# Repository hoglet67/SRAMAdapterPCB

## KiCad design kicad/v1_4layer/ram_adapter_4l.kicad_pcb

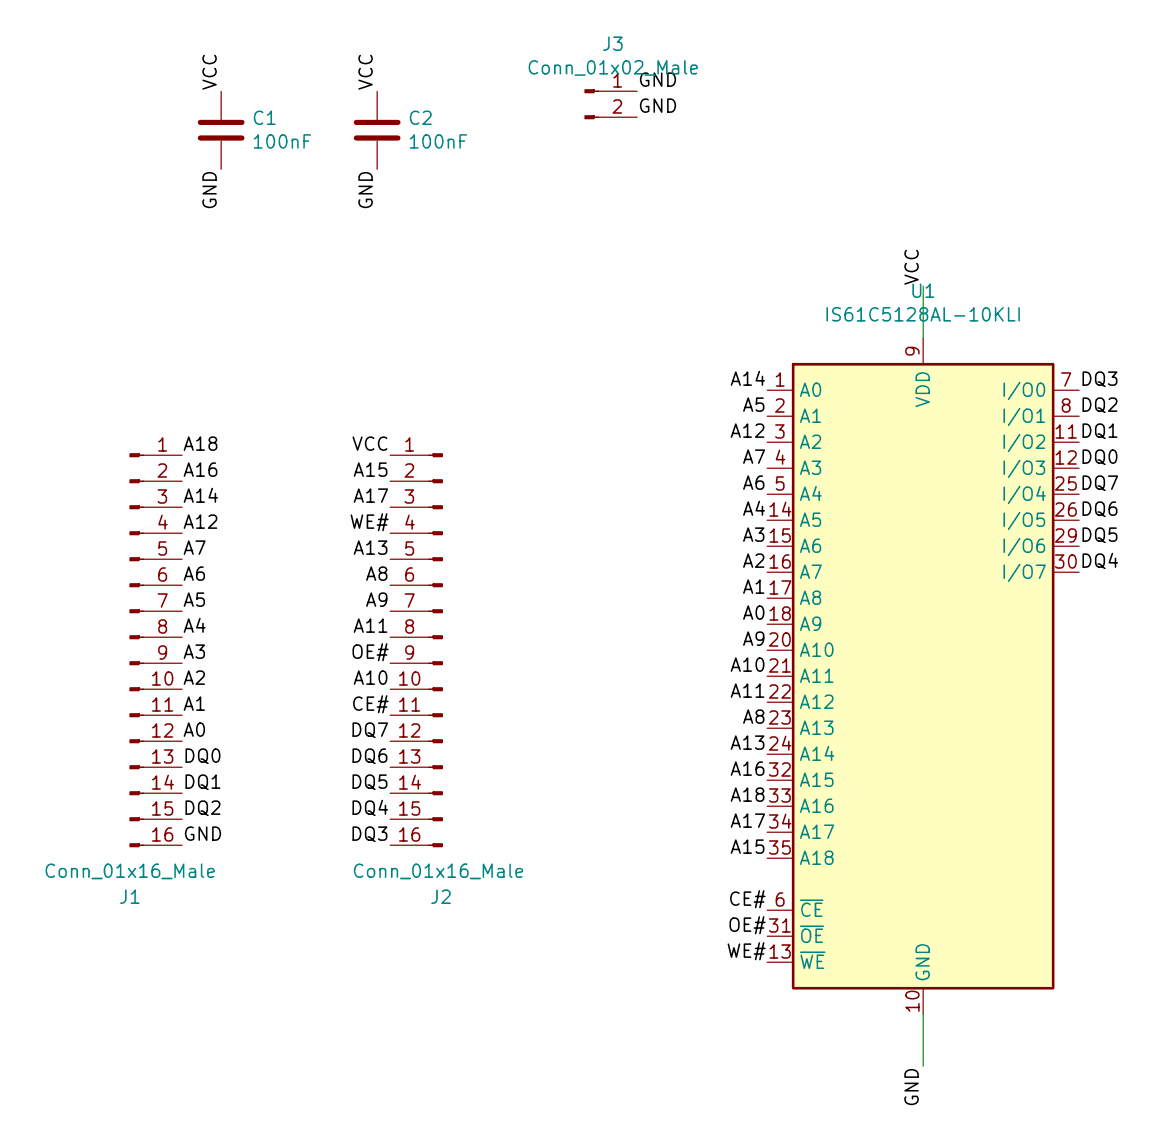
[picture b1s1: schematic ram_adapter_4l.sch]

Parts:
C1, C2: 100nF; C_0805_2012Metric
J1: Conn_01x16_Male; PinHeader_1x16_P2.54mm_Vertical
J2: Conn_01x16_Male; PinHeader_1x16_P2.54mm_VerticalAllRound
J3: Conn_01x02_Male; PinHeader_1x02_P2.54mm_Vertical
U1: IS61C5128AL-10KLI; SOJ-36_10.16x23.49mm_P1.27mm

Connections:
/A0: J1.12, U1.18 (A9)
/A1: J1.11, U1.17 (A8)
/A2: J1.10, U1.16 (A7)
/A3: J1.9, U1.15 (A6)
/A4: J1.8, U1.14 (A5)
/A5: J1.7, U1.2 (A1)
/A6: J1.6, U1.5 (A4)
/A7: J1.5, U1.4 (A3)
/A8: J2.6, U1.23 (A13)
/A9: J2.7, U1.20 (A10)
/A10: J2.10, U1.21 (A11)
/A11: J2.8, U1.22 (A12)
/A12: J1.4, U1.3 (A2)
/A13: J2.5, U1.24 (A14)
/A14: J1.3, U1.1 (A0)
/A15: J2.2, U1.35 (A18)
/A16: J1.2, U1.32 (A15)
/A17: J2.3, U1.34 (A17)
/A18: J1.1, U1.33 (A16)
/CE#: J2.11, U1.6 (~CE)
/DQ0: J1.13, U1.12 (I/O3)
/DQ1: J1.14, U1.11 (I/O2)
/DQ2: J1.15, U1.8 (I/O1)
/DQ3: J2.16, U1.7 (I/O0)
/DQ4: J2.15, U1.30 (I/O7)
/DQ5: J2.14, U1.29 (I/O6)
/DQ6: J2.13, U1.26 (I/O5)
/DQ7: J2.12, U1.25 (I/O4)
/GND: C1.2, C2.2, J1.16, J3.1, J3.2, U1.10 (GND), U1.28 (GND)
/OE#: J2.9, U1.31 (~OE)
/VCC: C1.1, C2.1, J2.1, U1.9 (VDD), U1.27 (VDD)
/WE#: J2.4, U1.13 (~WE)

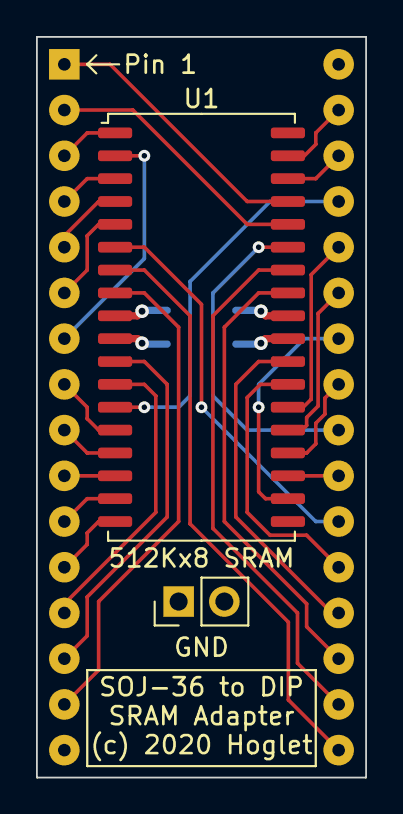
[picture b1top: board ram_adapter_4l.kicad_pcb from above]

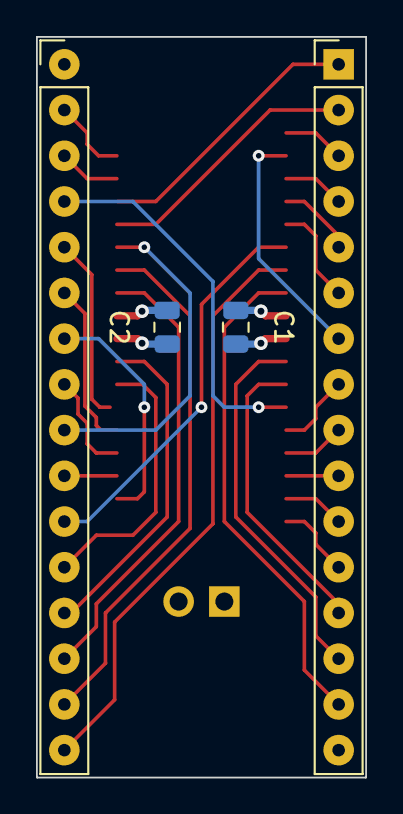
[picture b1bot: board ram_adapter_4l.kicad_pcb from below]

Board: 4 copper layers, 18.3 x 41.1 mm, 6 parts (4 on the bottom side), 32 nets.

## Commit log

2020-10-26 Initial commit of 2/4 layer versions
2020-10-26 Updated to 8/8 and 26/12 VIAs
2020-10-26 Renamed projeck ram_adapter_tsop->ram_adapter_4l
2020-10-26 Updated silk screen
2020-10-26 Extended SOJ pads by 0.2mm
2020-10-26 Tweak thermals
2020-10-26 Added ground points
2020-10-26 Added manufacturing outputs

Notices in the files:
kicad/v1_4layer/ram_adapter_4l.kicad_pcb:
(c) 2020 Hoglet
